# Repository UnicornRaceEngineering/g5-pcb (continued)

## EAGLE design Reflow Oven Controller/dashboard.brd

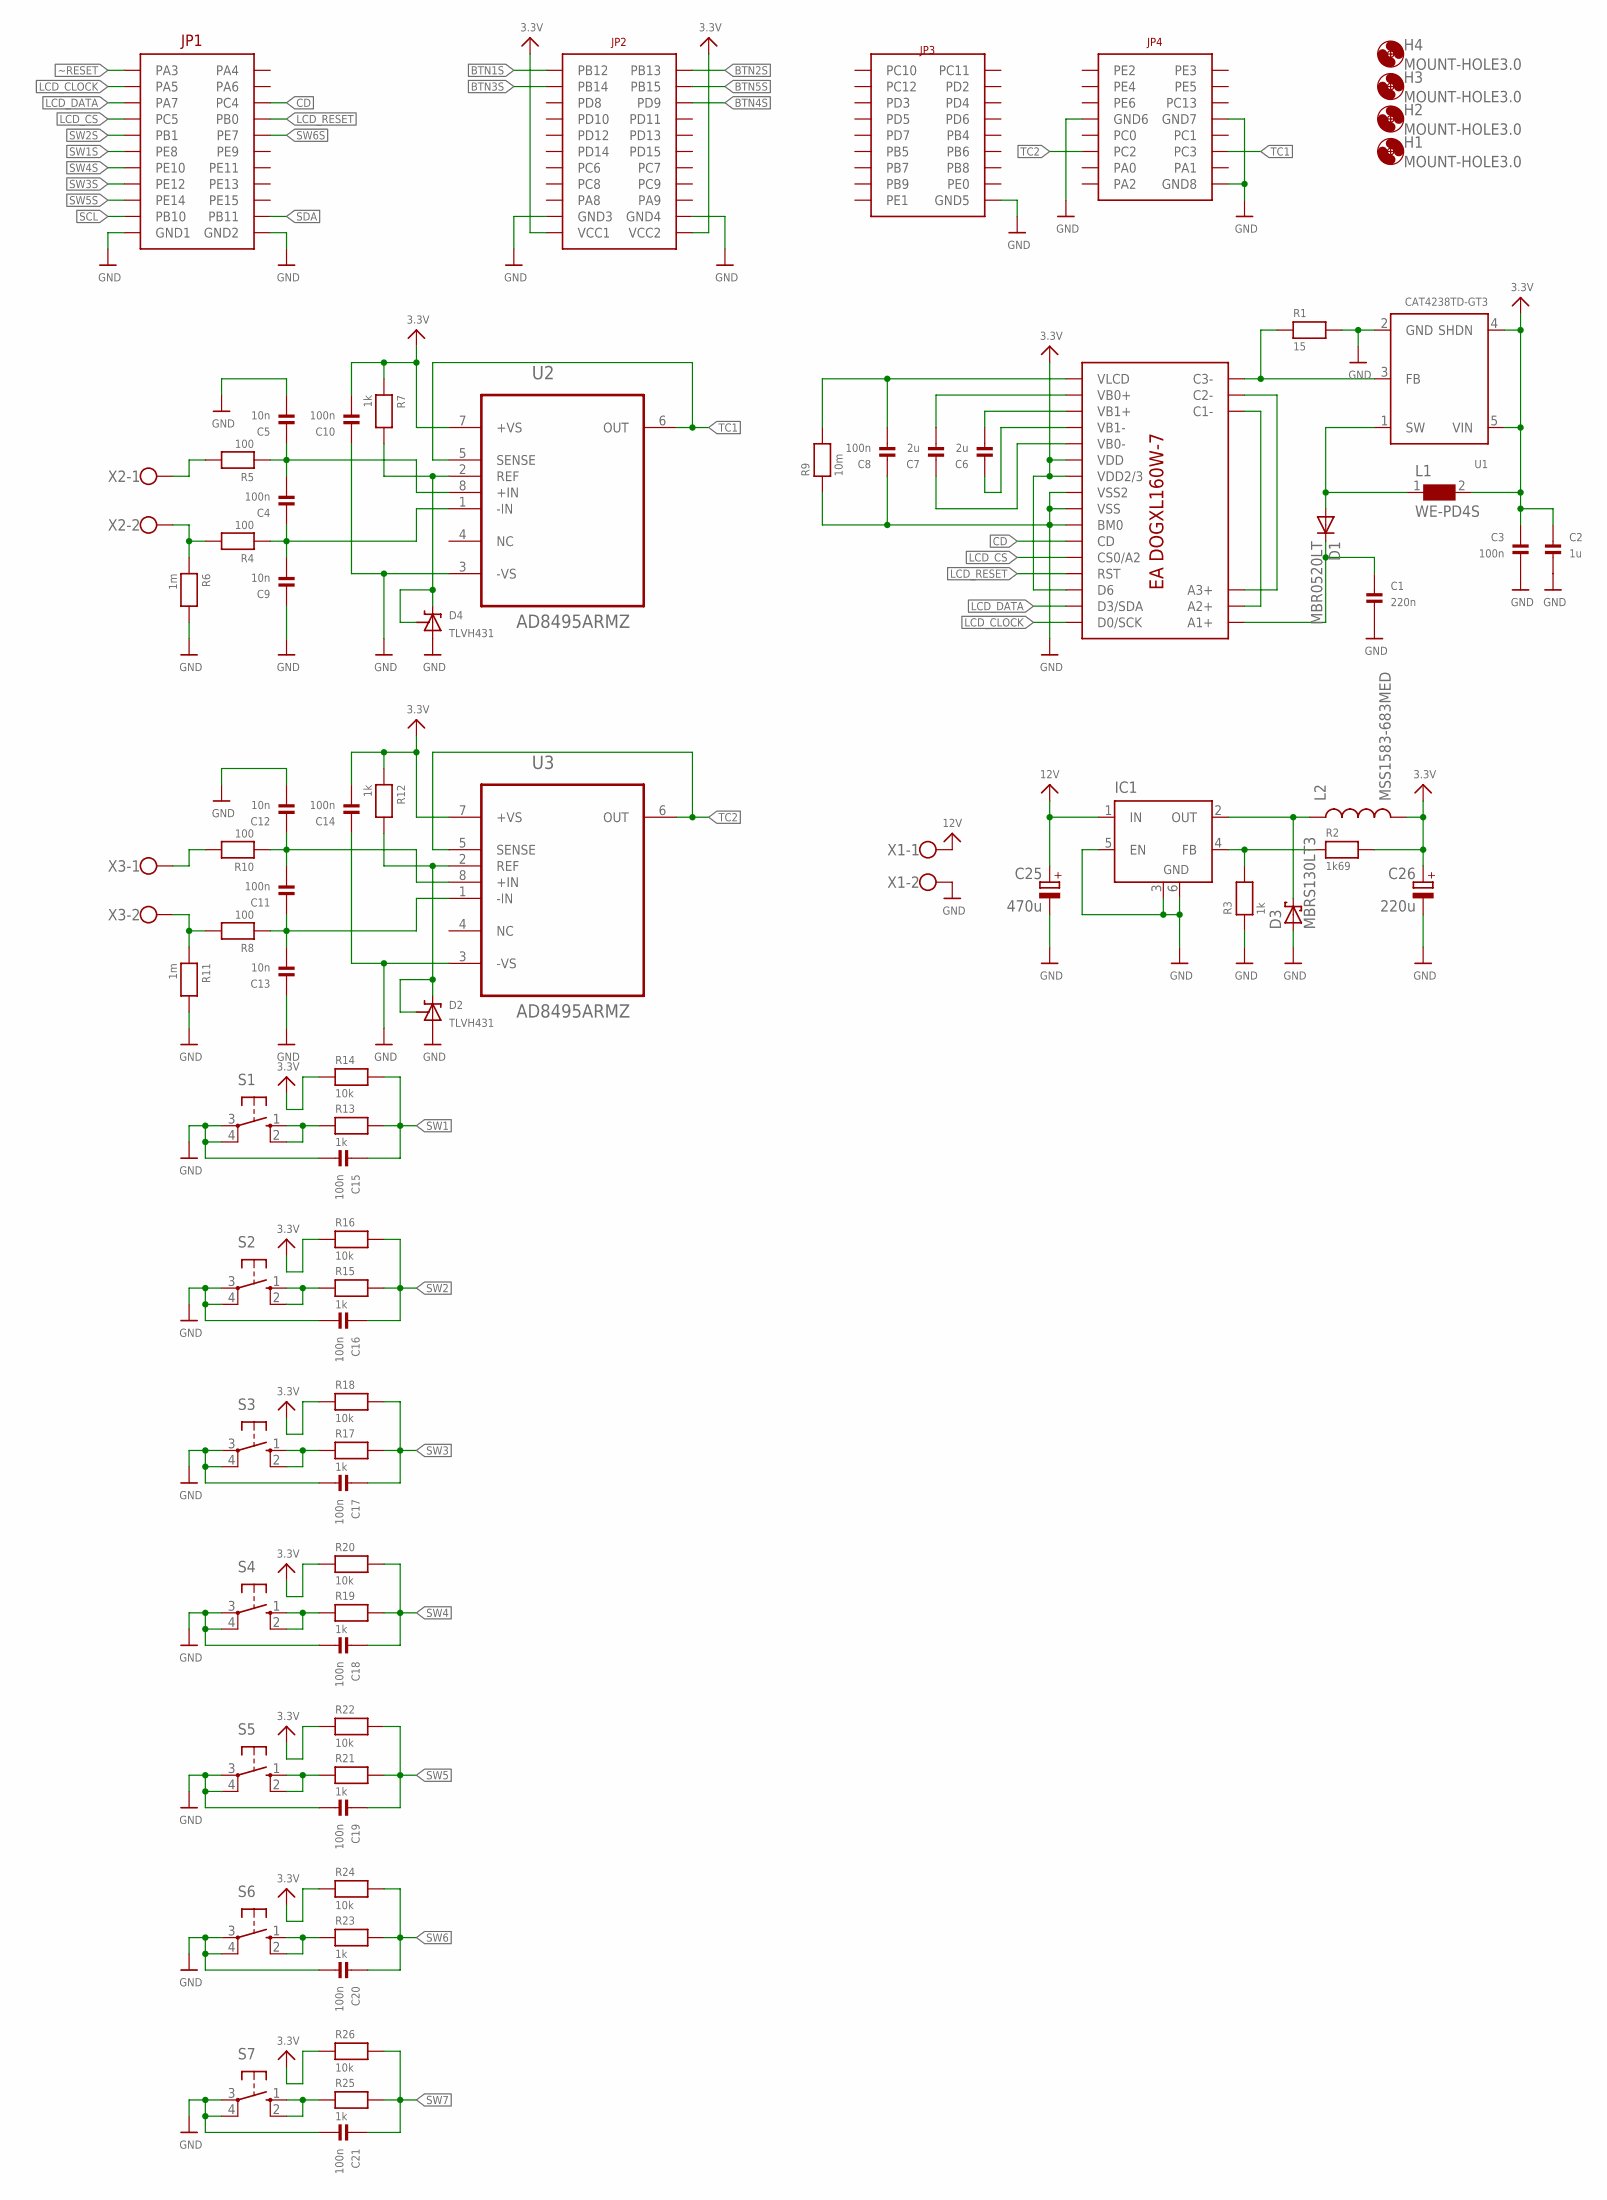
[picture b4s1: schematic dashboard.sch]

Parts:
C1: 220n; _0805
C2: 1u; _0805
C3, C4, C8, C10, C11, C14, C15, C16, C17, C18, C19, C20, C21: 100n; _0603
C5, C9, C12, C13: 10n; _0603
C6, C7: 2u; _0805
C25: 470u; 153CLV-1012
C26: 220u; 153CLV-1012
D1: MBR0520LT; SOD123
D2, D4: TLVH431; SOT23-R
D3: MBRS130LT3; SMB
H1, H2, H3, H4: MOUNT-HOLE3.0; 3,0
IC1: LM2596S; TO263-5
L1: WE-PD4S; S
L2: MSS1583-683MED; CDRH125
R1: 15; _0603
R2: 1k69; _0603
R3, R7, R12, R13, R15, R17, R19, R21, R23, R25: 1k; _0603
R4, R5, R8, R10: 100; _0603
R6, R11: 1m; _0603
R9: 10m; _0805
R14, R16, R18, R20, R22, R24, R26: 10k; _0603
S1, S2, S3, S4, S5, S6, S7: 10-XX; B3F-10XX
U1: CAT4238TD-GT3; SOT23-5
U2, U3: AD8495ARMZ; SOP65P490X110-8N
U$1: CPU-BOARD; CPU-BOARD-JP1
U$10: EA-DOGXL160W-7
X1, X2, X3: W237-102

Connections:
3.3V: C2.1, C3.1, C10.2, C14.2, C26.+, L1.2, L2.2, R2.2, R7.1, R12.1, R14.1, R16.1, R18.1, R20.1, R22.1, R24.1, R26.1, U1.4 (SHDN), U1.5 (VIN), U2.7 (+VS), U3.7 (+VS), U$1.P$43 (VCC1), U$1.P$44 (VCC2), U$10.P$22 (VDD), U$10.P$23 (VDD2/3), U$10.P$30 (D6)
12V: C25.+, IC1.1 (IN), X1.1
BTN1S: U$1.P$23 (PB12)
BTN2S: U$1.P$24 (PB13)
BTN3S: U$1.P$25 (PB14)
BTN4S: U$1.P$28 (PD9)
BTN5S: U$1.P$26 (PB15)
CD: U$1.P$6 (PC4), U$10.P$27 (CD)
GND: C1.2, C2.2, C3.2, C5.2, C8.1, C9.1, C10.1, C12.2, C13.1, C14.1, C15.2, C16.2, C17.2, C18.2, C19.2, C20.2, C21.2, C25.-, C26.-, D2.3 (A), D3.A, D4.3 (A), IC1.3 (GND), IC1.5 (EN), IC1.6 (GND), R1.2, R3.1, R6.2, R9.1, R11.2, S1.3, S1.4 (P1), S2.3, S2.4 (P1), S3.3, S3.4 (P1), S4.3, S4.4 (P1), S5.3, S5.4 (P1), S6.3, S6.4 (P1), S7.3, S7.4 (P1), U1.2 (GND), U2.3 (-VS), U3.3 (-VS), U$1.P$19 (GND1), U$1.P$20 (GND2), U$1.P$41 (GND3), U$1.P$42 (GND4), U$1.P$62 (GND5), U$1.P$69 (GND6), U$1.P$70 (GND7), U$1.P$78 (GND8), U$10.P$24 (VSS2), U$10.P$25 (VSS), U$10.P$26 (BM0), X1.2
LCD_CLOCK: U$1.P$3 (PA5), U$10.P$32 (D0/SCK)
LCD_CS: U$1.P$7 (PC5), U$10.P$28 (CS0/A2)
LCD_DATA: U$1.P$5 (PA7), U$10.P$31 (D3/SDA)
LCD_RESET: U$1.P$8 (PB0), U$10.P$29 (RST)
unnamed: U$10.P$2 (A2+), U$10.P$14 (C1-)
unnamed: U$10.P$3 (A3+), U$10.P$15 (C2-)
unnamed: R1.1, U1.3 (FB), U$10.P$16 (C3-)
unnamed: C1.1, D1.C, U$10.P$1 (A1+)
unnamed: D1.A, L1.1, U1.1 (SW)
unnamed: D3.C, IC1.2 (OUT), L2.1
unnamed: D2.1 (VREF), D2.2 (C), R12.2, U3.2 (REF)
unnamed: R15.1, S2.1 (S), S2.2 (S1)
unnamed: IC1.4 (FB), R2.1, R3.2
unnamed: D4.1 (VREF), D4.2 (C), R7.2, U2.2 (REF)
unnamed: R13.1, S1.1 (S), S1.2 (S1)
unnamed: C4.1, C9.2, R4.1, U2.1 (-IN)
unnamed: C11.1, C13.2, R8.1, U3.1 (-IN)
unnamed: R4.2, R6.1, X2.2
unnamed: R5.2, X2.1
unnamed: C4.2, C5.1, R5.1, U2.8 (+IN)
unnamed: R8.2, R11.1, X3.2
unnamed: R10.2, X3.1
unnamed: C11.2, C12.1, R10.1, U3.8 (+IN)
unnamed: R17.1, S3.1 (S), S3.2 (S1)
unnamed: R19.1, S4.1 (S), S4.2 (S1)
unnamed: R21.1, S5.1 (S), S5.2 (S1)
unnamed: R23.1, S6.1 (S), S6.2 (S1)
unnamed: R25.1, S7.1 (S), S7.2 (S1)
unnamed: C6.1, U$10.P$20 (VB1-)
unnamed: C7.1, U$10.P$21 (VB0-)
unnamed: C6.2, U$10.P$19 (VB1+)
unnamed: C7.2, U$10.P$18 (VB0+)
unnamed: C8.2, R9.2, U$10.P$17 (VLCD)
SCL: U$1.P$21 (PB10)
SDA: U$1.P$22 (PB11)
SW1: C15.1, R13.2, R14.2
SW1S: U$1.P$11 (PE8)
SW2: C16.1, R15.2, R16.2
SW2S: U$1.P$9 (PB1)
SW3: C17.1, R17.2, R18.2
SW3S: U$1.P$15 (PE12)
SW4: C18.1, R19.2, R20.2
SW4S: U$1.P$13 (PE10)
SW5: C19.1, R21.2, R22.2
SW5S: U$1.P$17 (PE14)
SW6: C20.1, R23.2, R24.2
SW6S: U$1.P$10 (PE7)
SW7: C21.1, R25.2, R26.2
TC1: U2.5 (SENSE), U2.6 (OUT), U$1.P$74 (PC3)
TC2: U3.5 (SENSE), U3.6 (OUT), U$1.P$73 (PC2)
~RESET: U$1.P$1 (PA3)

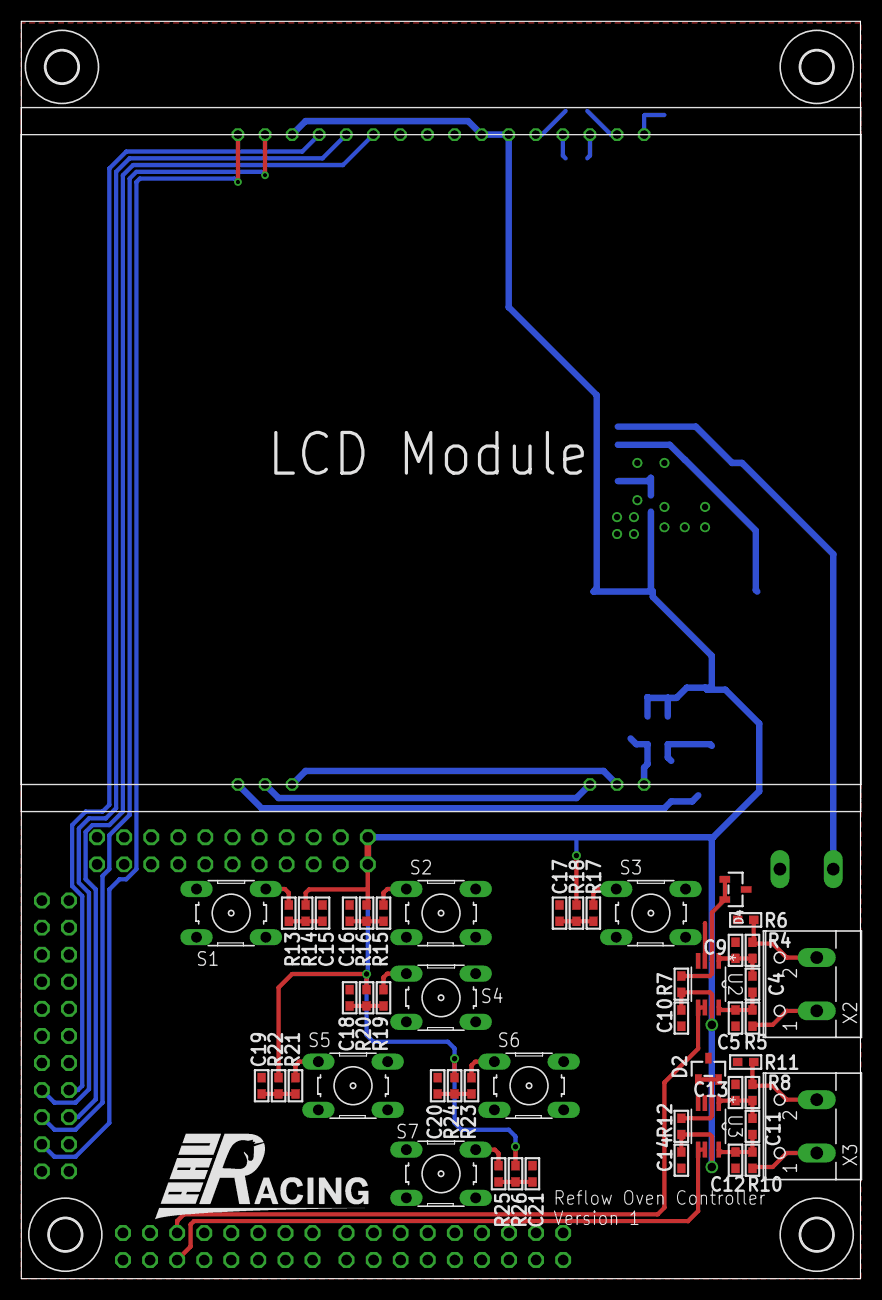
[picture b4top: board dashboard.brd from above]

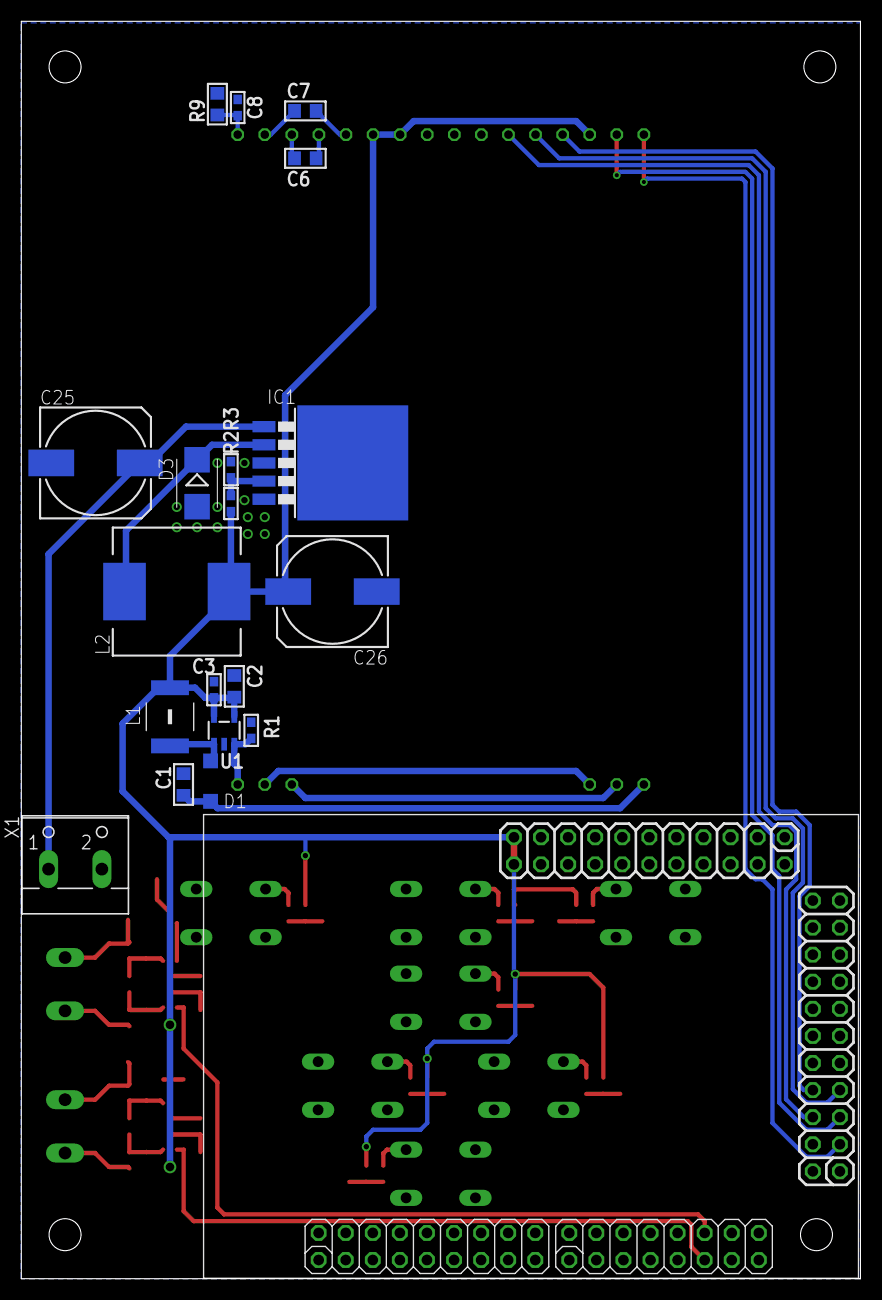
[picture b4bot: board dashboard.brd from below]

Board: 2 copper layers, 78.7 x 117.9 mm, 75 parts (20 on the bottom side), 46 nets.
